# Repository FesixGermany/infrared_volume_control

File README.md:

# Infrared volume control
 Digital audio volume controller for use with IR remote  

 ## Origin of project
 My friend pandora has a Philips TV with okay sound but not great. Would be nice to have some additional speakers.  
 Speakers can be connected to a headphone jack but volume can not be easily changed without entering two submenus of the TV.  
 The solution: Our own PCB with an IR receiver and an Arduino who decodes the commands "volume up" and "volume down" from the IR remote sent as RC6 protocol. These commands then are used to change the value of two digital potentiometers, one for each audio channel after the loudspeakers of the TV are diabled in the settings.

 ## Circuit
 TSOP34836 for demodulating the 36kHz IR signal, can be changed for other carrier frequencies.  
 Arduino nano clone with USB-C for all things digital.  
 MCP4151 digital potentiometer for attenuating audio level.  
 Inductors for filtering some noise on the power rails, especially when SPI is active.  
Resistors and capacitors for creating a virtual ground.  

## Housing
Simple 3D printed case, nothing fancy.

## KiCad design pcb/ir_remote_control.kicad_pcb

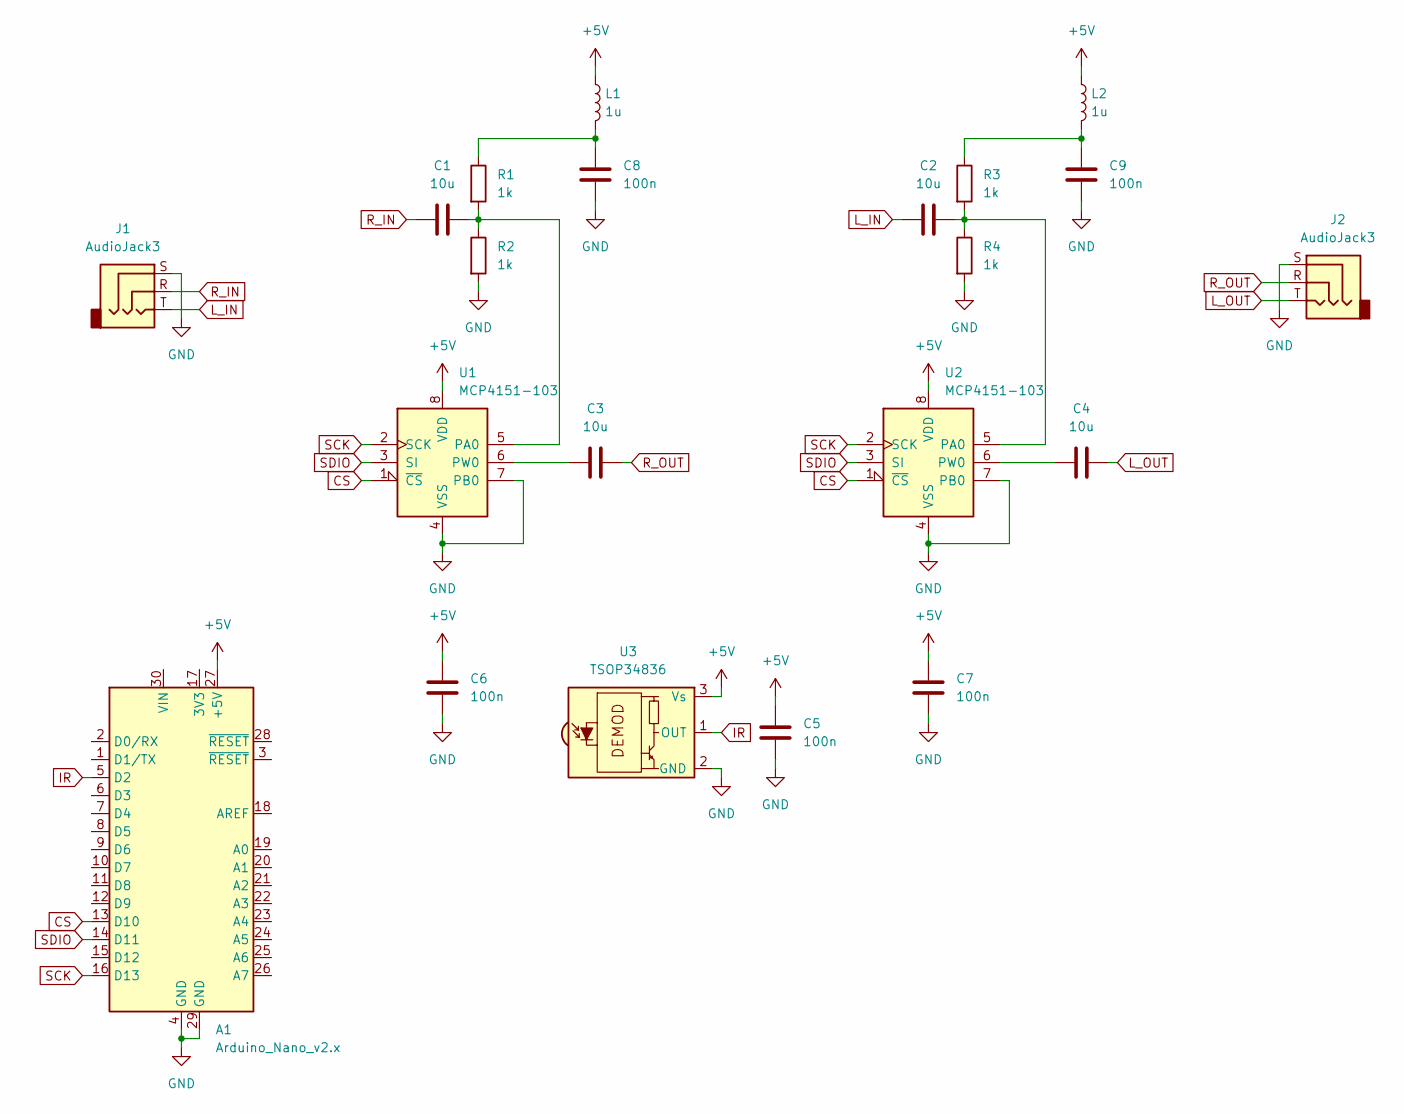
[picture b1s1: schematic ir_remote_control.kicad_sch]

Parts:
A1: Arduino_Nano_v2.x; Arduino_Nano
C1, C2, C3, C4: 10u; C_0805_2012Metric_Pad1.18x1.45mm_HandSolder
C5, C6, C7, C8, C9: 100n; C_0805_2012Metric_Pad1.18x1.45mm_HandSolder
J1, J2: AudioJack3; Jack_3.5mm_Switronic_ST-005-G_horizontal
L1, L2: 1u; L_0805_2012Metric_Pad1.15x1.40mm_HandSolder
R1, R2, R3, R4: 1k; R_0805_2012Metric_Pad1.20x1.40mm_HandSolder
U1, U2: MCP4151-103; DIP-8_W7.62mm
U3: TSOP34836; Vishay_MOLD-3Pin

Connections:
+5V: A1.27 (+5V), C5.1, C6.1, C7.1, L1.1, L2.1, U1.8 (VDD), U2.8 (VDD), U3.3 (Vs)
CS: A1.13 (D10), U1.1 (~CS), U2.1 (~CS)
GND: A1.4 (GND), A1.29 (GND), C5.2, C6.2, C7.2, C8.2, C9.2, J1.S, J2.S, R2.2, R4.2, U1.4 (VSS), U1.7 (PB0), U2.4 (VSS), U2.7 (PB0), U3.2 (GND)
IR: A1.5 (D2), U3.1 (OUT)
L_IN: C2.1, J1.T
L_OUT: C4.2, J2.T
unnamed: C8.1, L1.2, R1.1
unnamed: C9.1, L2.2, R3.1
unnamed: C1.2, R1.2, R2.1, U1.5 (PA0)
unnamed: C3.1, U1.6 (PW0)
unnamed: C2.2, R3.2, R4.1, U2.5 (PA0)
unnamed: C4.1, U2.6 (PW0)
R_IN: C1.1, J1.R
R_OUT: C3.2, J2.R
SCK: A1.16 (D13), U1.2 (SCK), U2.2 (SCK)
SDIO: A1.14 (D11), U1.3 (SI), U2.3 (SI)

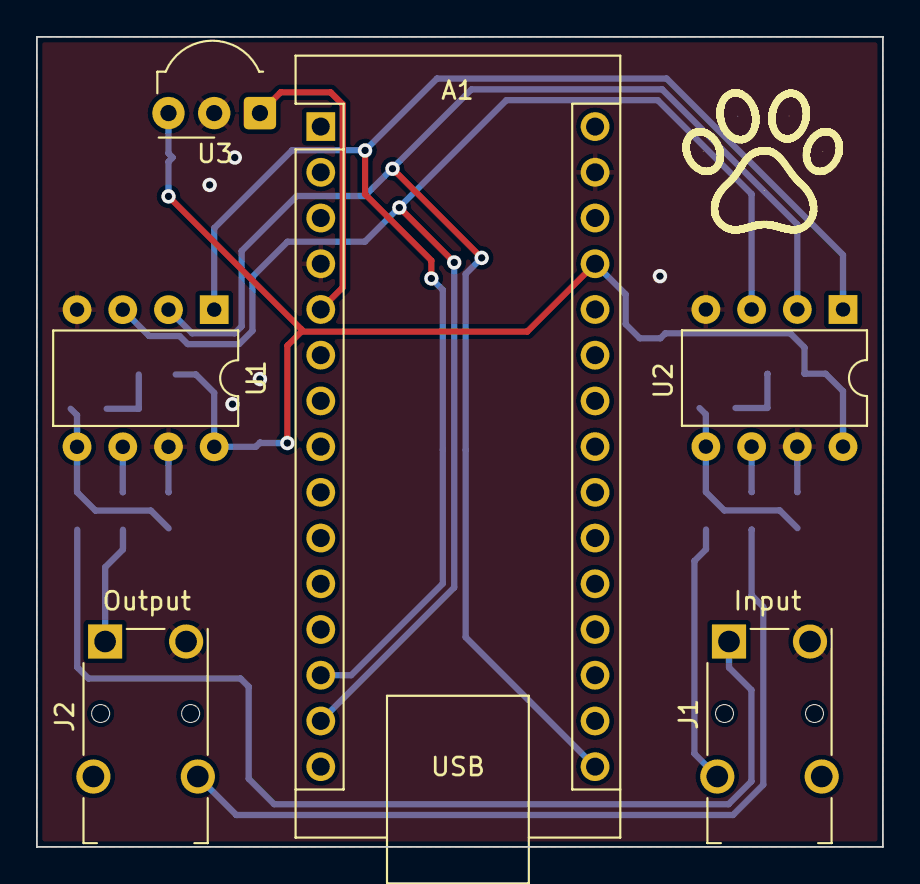
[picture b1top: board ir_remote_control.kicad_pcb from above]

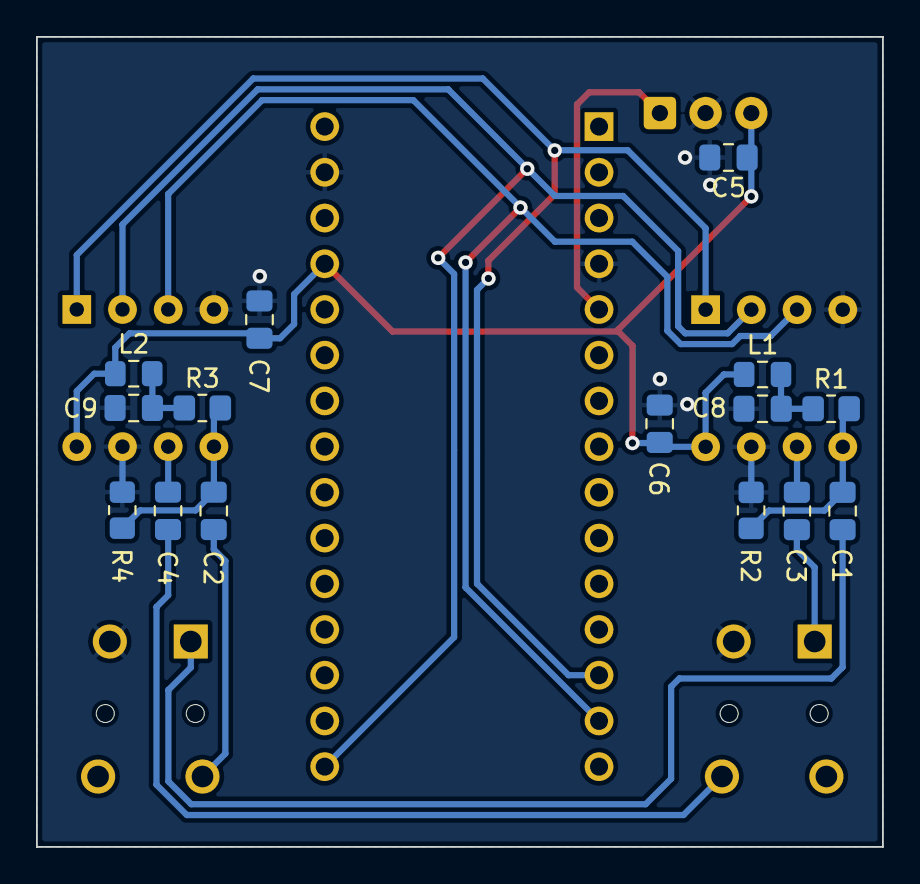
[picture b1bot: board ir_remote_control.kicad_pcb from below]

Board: 2 copper layers, 47.0 x 45.0 mm, 21 parts (15 on the bottom side), 16 nets.

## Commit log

2024-02-17 project complete
